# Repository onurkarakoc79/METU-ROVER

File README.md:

# METU Rover Project (2019–2022)
# Overview
The METU Rover project focuses on developing advanced robotics solutions for exploration, object detection, and autonomous navigation. During my involvement from 2019 to 2022, I contributed to various aspects of the project, including hardware integration, software development, and algorithm optimization.

# Features

* Object Detection: Implemented temperature-initiated object detection algorithms.
* Autonomous Navigation: Enhanced path planning and obstacle avoidance mechanisms.
* Modular Design: Ensured scalability and modularity in system design.

Setup Instructions
To clone the repository for one of my published modules:

```bash
   git clone https://github.com/onurkarakoc79/METU-ROVER
```
About METU Rover
Learn more about the METU Rover project at METU Rover Website.

<pre> https://meturover.com </pre>

## Contact

If you have any questions, feedback, or inquiries related to the project, feel free to reach out to me:

My personal mail: onurkarakoc79@gmail.com

I appreciate your interest in my projects and look forward to collaborating with you in the fascinating field of scientific exploration and discovery.

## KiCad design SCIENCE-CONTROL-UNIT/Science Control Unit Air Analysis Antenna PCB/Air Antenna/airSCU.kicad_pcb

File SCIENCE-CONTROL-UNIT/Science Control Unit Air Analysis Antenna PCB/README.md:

# PCB for Antenna Control and Sensor Interface
## What is the PCB Made For

The PCB designed for the antenna serves as a control card, providing essential functionality for the antenna system. It incorporates an STM32 microcontroller, six sensor inputs, and a CAN module for seamless communication with the host system. The antenna system is capable of detecting gases such as CO, CH4, and H2 using these sensors. Additionally, it can measure UV light intensity, airborne dust levels, and accurately determine air temperature and humidity. The STM32 processor reads and organizes the data from the sensors, which is then transmitted to the central control unit via the CAN module. From there, the data flows to the rover host (Nvidia Jetson TX2) and ultimately reaches the central control center with the assistance of Lora communication. The collected data is utilized for the projected thesis or other relevant purposes.

## PCB Description
The PCB designed for the antenna system exhibits a straightforward structure with the following features:

Sensor Inputs: The PCB provides six JST inputs for connecting the sensors. To ensure compatibility with the 3.3V operating voltage of the STM32 microcontroller, a voltage divider is implemented for sensor outputs that typically work with 5 volts.

Layer Structure: The PCB follows a 2-layer design. The first layer is dedicated to the 5V field, while the second layer is covered with the GND field, establishing a proper grounding structure.

Power Supply: Although the main power input to the PCB is 24V, a voltage regulator is employed to reduce the voltage to 5V, which is then supplied to the sensors. This ensures the sensors operate within their specified voltage range.

Interchangeability and Assembly: Instead of utilizing SMD components, the PCB is designed to accommodate female header pins, enabling easy assembly and interchangeability. This design choice allows the PCB to function as a basic breadboard and facilitates the placement of a ready-made STM32 Blue Pill module on it. 

As a result, the system can be used without the need for voltage level conversion from 5V to 3.3V for the STM32 microcontroller.
Please note that this is a summary of the key features of the antenna PCB. For more detailed technical specifications and information, please refer to the relevant documentation.

## Contact

If you have any questions, feedback, or inquiries related to the project, feel free to reach out to me:

My personal mail: onurkarakoc79@gmail.com

I appreciate your interest in my projects and look forward to collaborating with you in the fascinating field of scientific exploration and discovery.

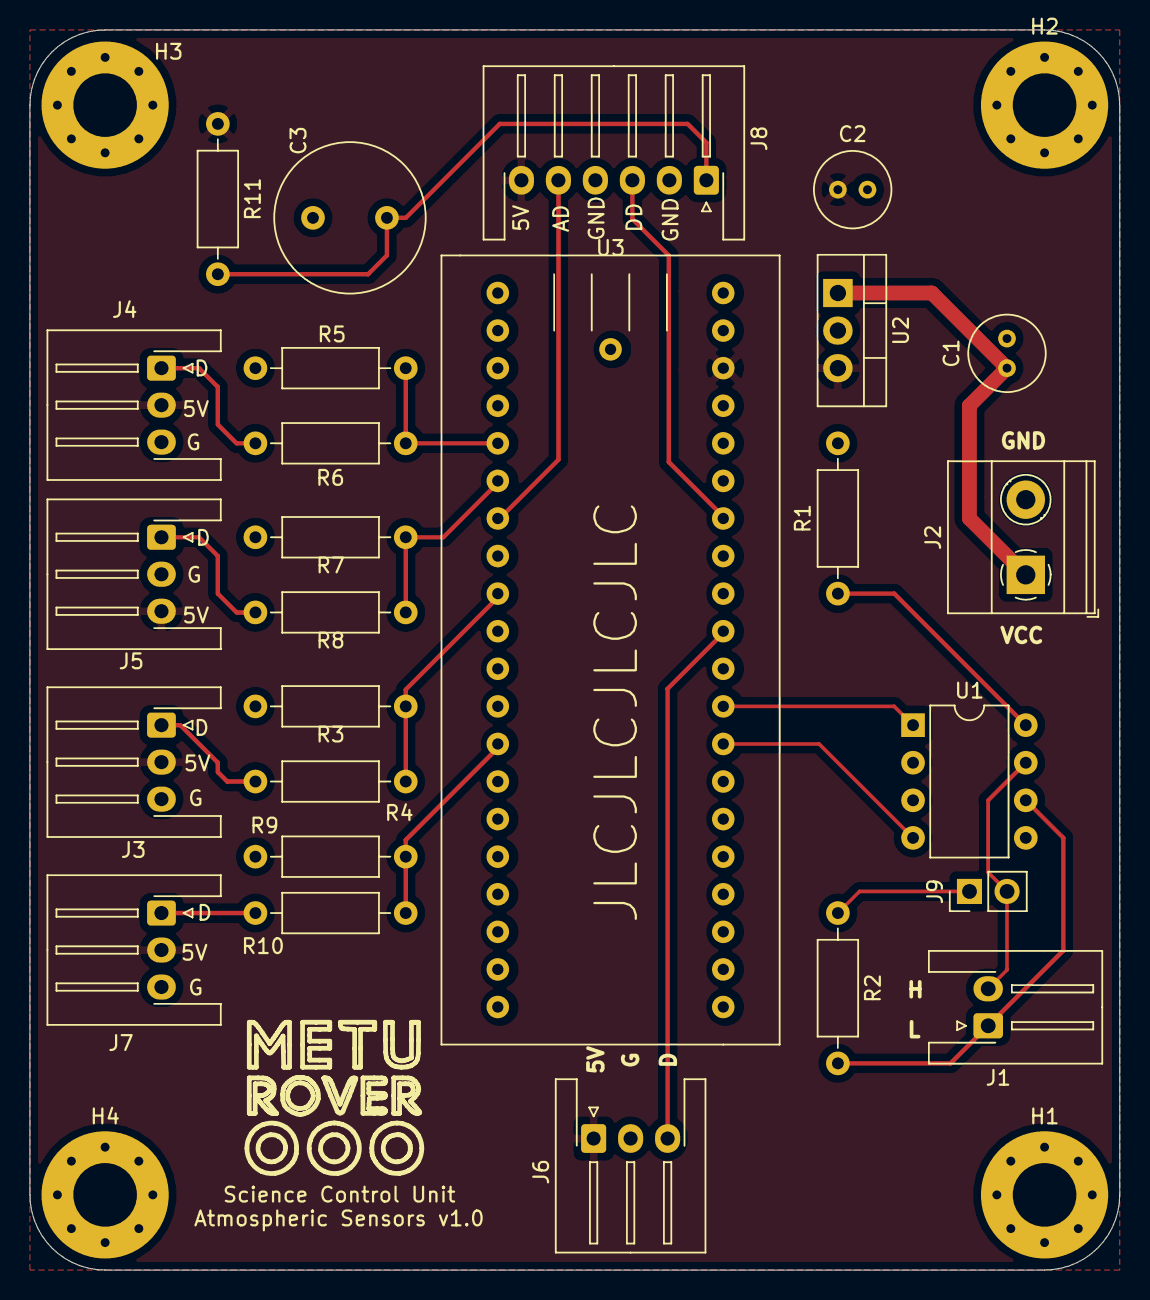
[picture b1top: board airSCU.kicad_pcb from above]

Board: 2 copper layers, 73.7 x 83.8 mm, 30 parts (0 on the bottom side), 21 nets.

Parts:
C1: 0.33u; C_Radial_D5.0mm_H5.0mm_P2.00mm
C2: 0.1u; C_Radial_D5.0mm_H5.0mm_P2.00mm
C3: 220uF; C_Radial_D10.0mm_H12.5mm_P5.00mm
H1, H2, H3, H4: MountingHole_Pad; MountingHole_4.3mm_M4_Pad_Via
J1: CAN_conn; JST_XH_S2B-XH-A-1_1x02_P2.50mm_Horizontal
J2: Power Connection; TerminalBlock_Phoenix_MKDS-1,5-2-5.08_1x02_P5.08mm_Horizont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
J3: CO Sensor; JST_XH_S3B-XH-A-1_1x03_P2.50mm_Horizontal
J4: UV Sensor; JST_XH_S3B-XH-A-1_1x03_P2.50mm_Horizontal
J5: H2 Sensor; JST_XH_S3B-XH-A-1_1x03_P2.50mm_Horizontal
J6: DHT22 Temperture Sensor; JST_XH_S3B-XH-A-1_1x03_P2.50mm_Horizontal
J7: CH4 Sensor; JST_XH_S3B-XH-A-1_1x03_P2.50mm_Horizontal
J8: Optical Dust Sensor; JST_XH_S6B-XH-A-1_1x06_P2.50mm_Horizontal
J9: res_selector; PinHeader_1x02_P2.54mm_Vertical
R1, R4, R6, R8, R10: 10k; R_Axial_DIN0207_L6.3mm_D2.5mm_P10.16mm_Horizontal
R2: 120r; R_Axial_DIN0207_L6.3mm_D2.5mm_P10.16mm_Horizontal
R3, R5, R7, R9: 20k; R_Axial_DIN0207_L6.3mm_D2.5mm_P10.16mm_Horizontal
R11: 150; R_Axial_DIN0207_L6.3mm_D2.5mm_P10.16mm_Horizontal
U1: MCP2551-I-P; DIP-8_W7.62mm
U2: LM78M05_TO220; TO-220-3_Vertical
U3: blue_pill

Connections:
+5V: C2.1, J3.2, J4.2, J5.3, J6.1, J7.2, J8.6, R11.1, U2.3, U3.3
CANH: J1.2, J9.2, U1.7
CANL: J1.1, R2.2, U1.6
CH4A0: R9.2, R10.1, U3.28
COA0: R3.2, R4.1, U3.32
DHT22D0: J6.3, U3.10
GND: C1.2, C2.2, C3.2, H1.1, H2.1, H3.1, H4.1, J2.2, J3.3, J4.3, J5.2, J6.2, J7.3, J8.2, J8.4, R1.2, R3.1, R5.1, R7.1, R9.1, U2.2, U3.2, U3.21, U3.22
H2A0: R7.2, R8.1, U3.35
unnamed: C3.1, J8.1, R11.2
unnamed: J3.1, R4.2
unnamed: J4.1, R6.2
unnamed: J5.1, R8.2
unnamed: J7.1, R10.2
unnamed: J9.1, R2.1
unnamed: R1.1, U1.8
ODSA0: J8.5, U3.34
ODSD0: J8.3, U3.7
UVA0: R5.2, R6.1, U3.36
VCC: C1.1, J2.1, U2.1
can_rx: U1.4, U3.13
can_tx: U1.1, U3.12

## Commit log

2023-07-13 Rename ReadMeFile.txt to ReadMeFile.md
2023-07-13 Rename ReadMeFile.md to README.md
